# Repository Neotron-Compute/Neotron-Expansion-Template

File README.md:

# Neotron Expansion Template

This repository contains a template PCB you can use as the start of a new Neotron Expansion Card design.

It contains an MCP23S17 SPI I/O expander, connected to the SPI bus. It also contains an I²C EEPROM connected to the I²C bus and the unique slot address lines. The I/O expander has eight LEDs and eight switches fitted.

There is a jumper which will allow you to program the EEPROM from your Neotron system. Normally this jumper is not fitted, making the EEPROM read-only. The contents of the EEPROM are TBD, but will describe the expansion card to the Neotron OS so that it can be auto-configured and any necessary drivers loaded.

## Using this template

To use this template, simply copy the files in this repository and edit away! You'll probably want to delete everything on the schematic except the edge connector and the EEPROM (unless you really need an SPI I/O exander...).

## Licence

This schematic and PCB design is Copyright (c) 2022 The Neotron Developers, et al.

This work is licensed under a [Creative Commons Attribution 4.0 International License](http://creativecommons.org/licenses/by/4.0/).

## Contribution Agreement

Unless you explicitly state otherwise, any contribution intentionally submitted for inclusion in the work by you, as defined in the Apache-2.0 license, shall be licensed as above, without any additional terms or conditions.

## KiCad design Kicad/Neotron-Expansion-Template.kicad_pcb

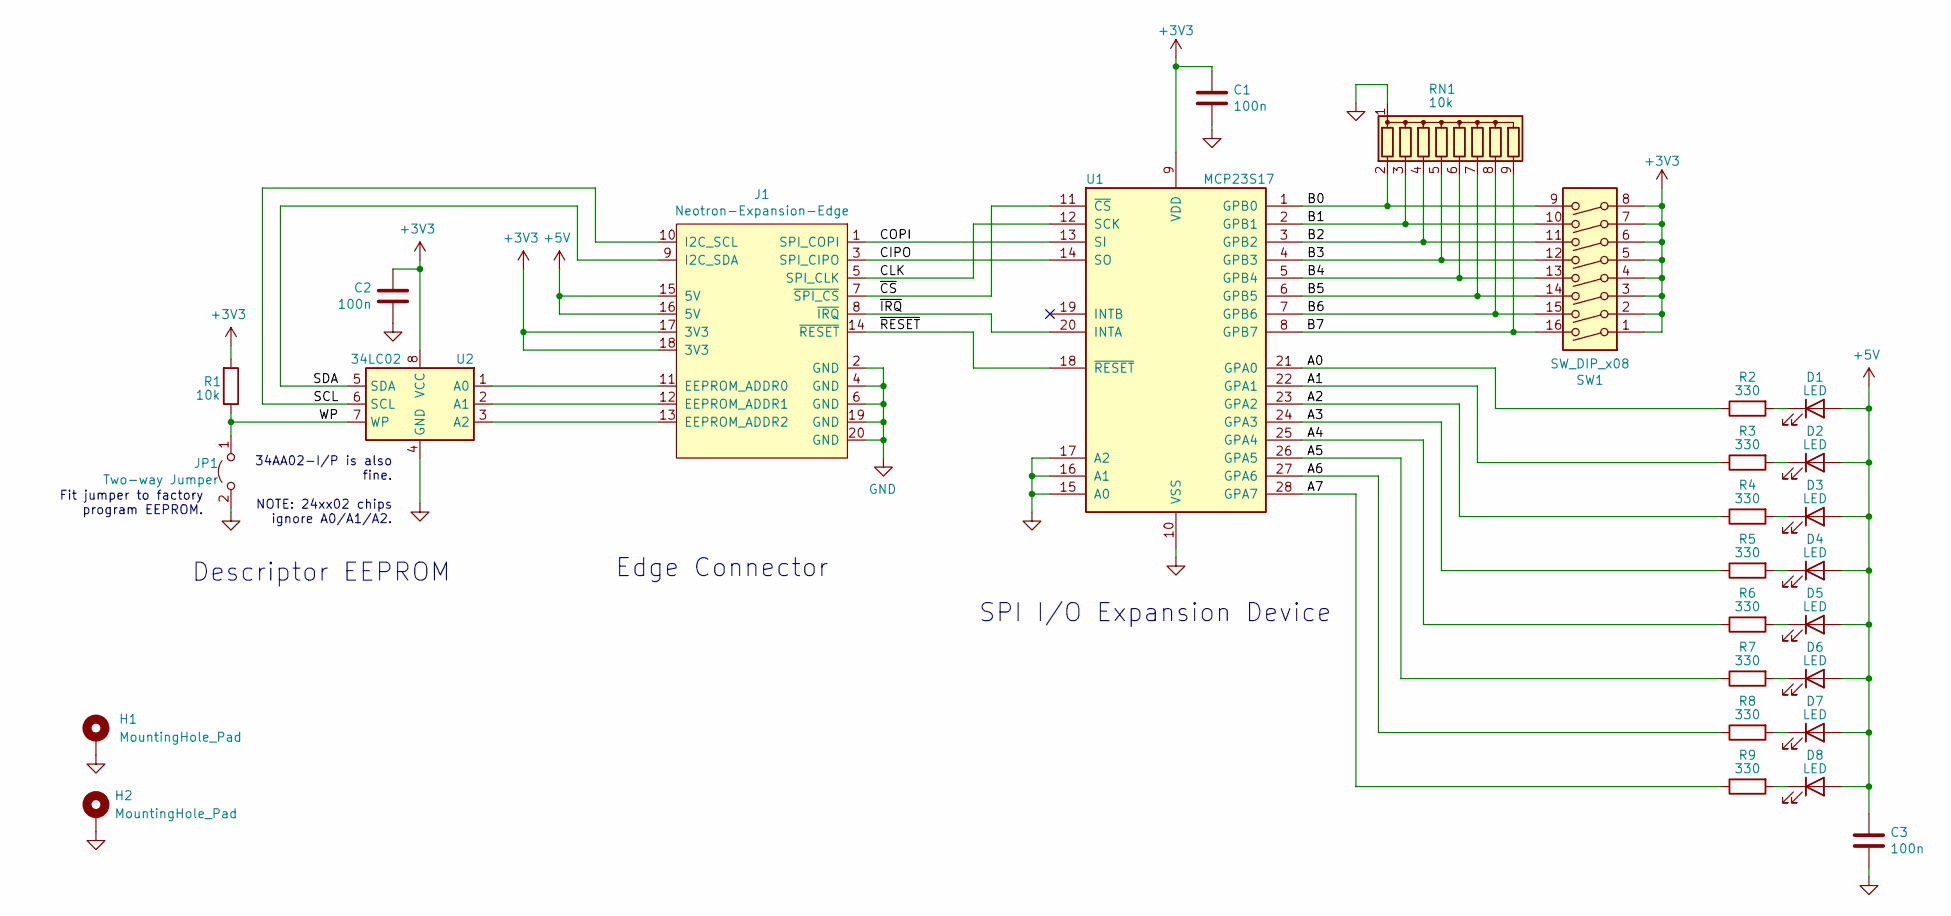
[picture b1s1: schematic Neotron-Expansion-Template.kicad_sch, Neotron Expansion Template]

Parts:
C1, C2: 100n; C_Disc_D7.0mm_W2.5mm_P5.00mm; Voltage 10V; MPN C315C104M5U5TA; Digikey 399-4151-ND
C3: 100n; C_Disc_D7.0mm_W2.5mm_P5.00mm; Voltage 16V; MPN C315C104M5U5TA; Digikey 399-4151-ND
D1, D2, D3, D4, D5, D6, D7, D8: LED; LED_D3.0mm; MPN L314ED; Digikey 2460-L314ED-ND
H1, H2: MountingHole_Pad; MountingHole_2.7mm_M2.5_Pad
J1: Neotron-Expansion-Edge
JP1: Two-way Jumper; PinHeader_1x02_P2.54mm_Vertical
R1: 10k; R_Axial_DIN0207_L6.3mm_D2.5mm_P10.16mm_Horizontal; MPN CF14JT10K0; Digikey CF14JT10K0TR-ND
R2, R3, R4, R5, R6, R7, R8, R9: 330; R_Axial_DIN0207_L6.3mm_D2.5mm_P10.16mm_Horizontal; MPN CF14JT330R; Digikey CF14JT330RTR-ND
RN1: 10k; R_Array_SIP9; MPN 4609X-101-103LF; Digikey 4609X-101-103LF-ND
SW1: SW_DIP_x08; DIP-16_W7.62mm_LongPads; MPN DS01C-254-L-08BE; Digikey 2223-DS01C-254-L-08BE-ND
U1: MCP23S17; DIP-28_W7.62mm; MPN MCP23S17-E/SP; Digikey MCP23S17-E/SP-ND
U2: 34LC02; DIP-8_W7.62mm; MPN 34LC02-I/P; Digikey 34LC02-I/P-ND

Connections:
+3V3: C1.1, C2.1, J1.17 (3V3), J1.18 (3V3), R1.2, SW1.1, SW1.2, SW1.3, SW1.4, SW1.5, SW1.6, SW1.7, SW1.8, U1.9 (VDD), U2.8 (VCC)
+5V: C3.1, D1.2 (A), D2.2 (A), D3.2 (A), D4.2 (A), D5.2 (A), D6.2 (A), D7.2 (A), D8.2 (A), J1.15 (5V), J1.16 (5V)
/A0: R2.1, U1.21 (GPA0)
/A1: R3.1, U1.22 (GPA1)
/A2: R4.1, U1.23 (GPA2)
/A3: R5.1, U1.24 (GPA3)
/A4: R6.1, U1.25 (GPA4)
/A5: R7.1, U1.26 (GPA5)
/A6: R8.1, U1.27 (GPA6)
/A7: R9.1, U1.28 (GPA7)
/B0: RN1.2 (R1), SW1.9, U1.1 (GPB0)
/B1: RN1.3 (R2), SW1.10, U1.2 (GPB1)
/B2: RN1.4 (R3), SW1.11, U1.3 (GPB2)
/B3: RN1.5 (R4), SW1.12, U1.4 (GPB3)
/B4: RN1.6 (R5), SW1.13, U1.5 (GPB4)
/B5: RN1.7 (R6), SW1.14, U1.6 (GPB5)
/B6: RN1.8 (R7), SW1.15, U1.7 (GPB6)
/B7: RN1.9 (R8), SW1.16, U1.8 (GPB7)
/CIPO: J1.3 (SPI_CIPO), U1.14 (SO)
/CLK: J1.5 (SPI_CLK), U1.12 (SCK)
/COPI: J1.1 (SPI_COPI), U1.13 (SI)
/SCL: J1.10 (I2C_SCL), U2.6 (SCL)
/SDA: J1.9 (I2C_SDA), U2.5 (SDA)
/WP: JP1.1 (A), R1.1, U2.7 (WP)
/~CS: J1.7 (~SPI_CS), U1.11 (~CS)
/~IRQ: J1.8 (~IRQ), U1.20 (INTA)
/~RESET: J1.14 (~RESET), U1.18 (~RESET)
GND: C1.2, C2.2, C3.2, H1.1, H2.1, J1.2 (GND), J1.4 (GND), J1.6 (GND), J1.19 (GND), J1.20 (GND), JP1.2 (B), RN1.1 (common), U1.10 (VSS), U1.15 (A0), U1.16 (A1), U1.17 (A2), U2.4 (GND)
unnamed: D1.1 (K), R2.2
unnamed: D2.1 (K), R3.2
unnamed: D3.1 (K), R4.2
unnamed: D4.1 (K), R5.2
unnamed: D5.1 (K), R6.2
unnamed: D6.1 (K), R7.2
unnamed: D7.1 (K), R8.2
unnamed: D8.1 (K), R9.2
unnamed: J1.11 (EEPROM_ADDR0), U2.1 (A0)
unnamed: J1.12 (EEPROM_ADDR1), U2.2 (A1)
unnamed: J1.13 (EEPROM_ADDR2), U2.3 (A2)

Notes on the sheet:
Edge Connector
34AA02-I/P is also fine. NOTE: 24xx02 chips ignore A0/A1/A2.
Descriptor EEPROM
Fit jumper to factory program EEPROM.
SPI I/O Expansion Device

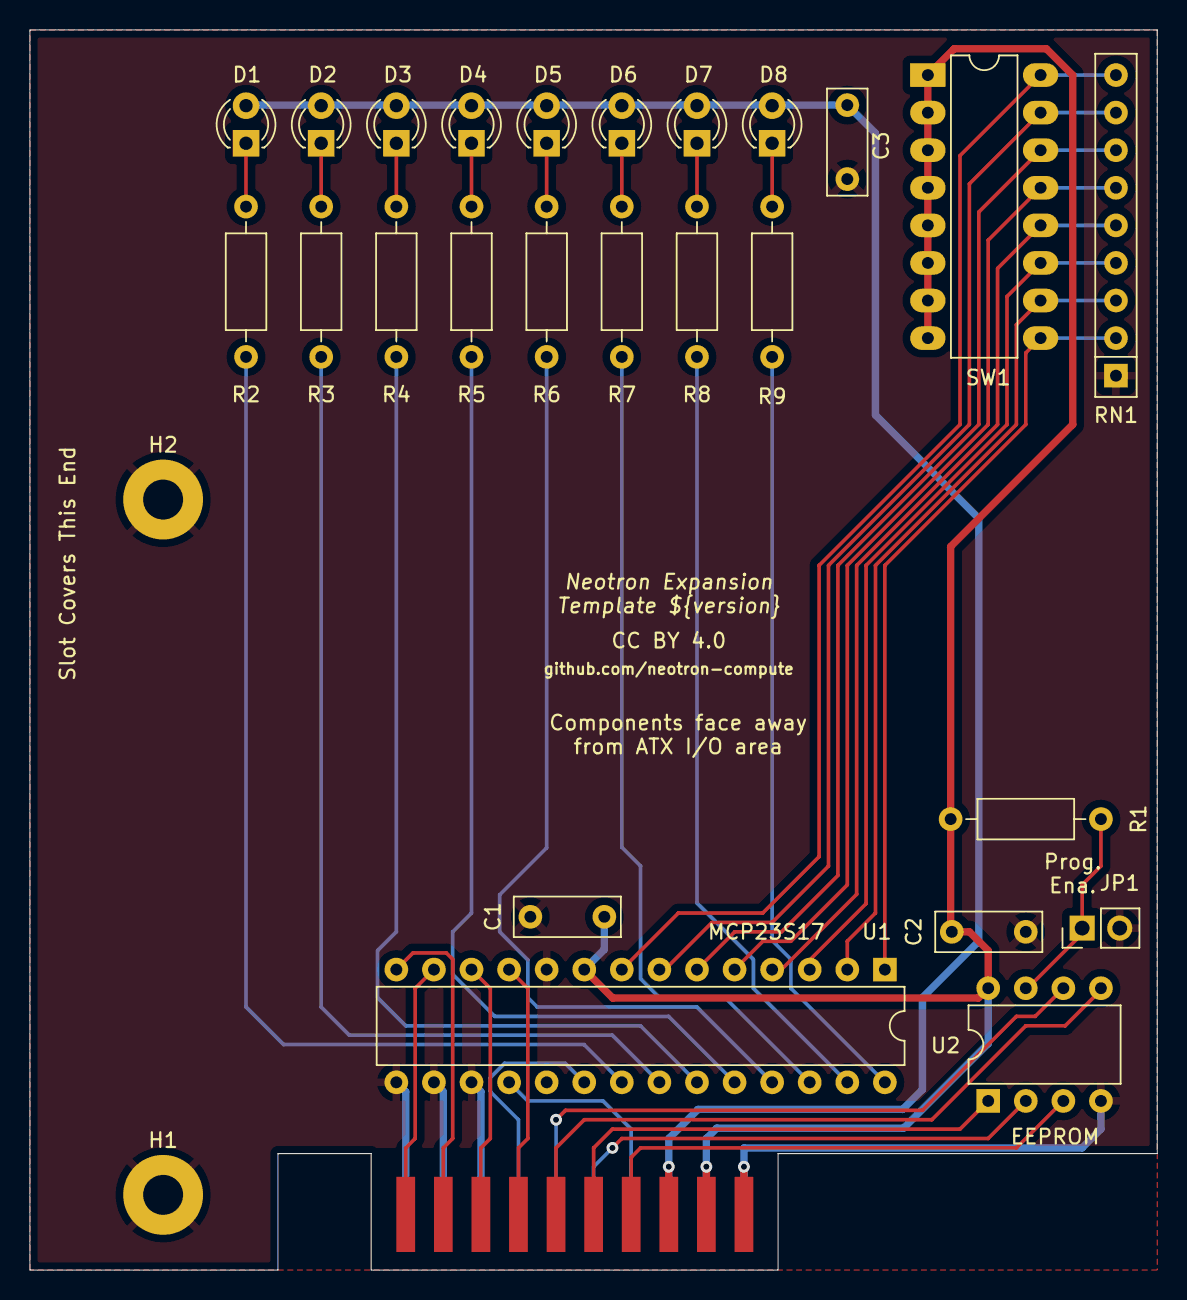
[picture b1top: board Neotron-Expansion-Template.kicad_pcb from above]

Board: 2 copper layers, 76.2 x 83.8 mm, 28 parts (0 on the bottom side), 39 nets.

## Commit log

2021-08-18 First draft.
2021-08-18 Add kicad-exports.
2021-08-18 root commit
2021-08-18 Added a CHANGELOG
2022-07-22 Updated to KiCAD 6 and re-worked.
    Power is the right way around now....
2022-07-22 Bring over new CI code.
    Taken from Neotron Pico.
2022-07-22 Update changelog
2022-07-23 Fix date/version fields.
    They must be set as ${field}, so Kibot can replace them.
2022-07-29 Adjusted board size to suit Neotron Pico 1.0.0.
    Has holes for a random backplate I found.
2022-07-29 DRC/ERC backwards.
    -s means "skip".
2022-07-29 Fix DRC issues.

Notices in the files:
Kicad/Neotron-Expansion-Template.kicad_pcb:
Licenced as CC BY 4.0
CC BY 4.0
Kicad/Neotron-Expansion-Template.kicad_sch:
Licensed as CC BY 4.0
Copyright (c) 2021, The Neotron Developers, et al.
